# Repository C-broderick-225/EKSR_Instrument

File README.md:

# EKSR_Instrument (Fork)

**This repository is a fork of the original [EKSR_Instrument](https://github.com/magicmicros/EKSR_Instrument) project.**

## Overview
This project serves as the foundation for a new product based on the EKSR_Instrument hardware and firmware. It utilizes an ESP32-S3 microcontroller to receive and decode messages from FarDriver motor controllers over BLE, and displays the processed data on a 2.4" TFT touchscreen display.

## ESP32-S3 BLE Multi-Role Support
The ESP32-S3 (including the ESP32-S3-WROOM-1 module) is capable of acting as both a BLE client (central) and a BLE server (peripheral) simultaneously. This allows the device to connect to a BLE peripheral (such as a Far Driver controller) while also advertising its own BLE service for other clients (such as an Android phone) to connect and receive forwarded data. This multi-role (dual-role) capability is officially supported by Espressif and is useful for BLE proxy/bridge applications.

**Key facts:**
- The ESP32-S3 can operate as both a BLE client and server at the same time (multi-role topology).
- This is supported by the ESP-IDF and ESP-NimBLE host stack.
- Example use case: ESP32-S3 connects to a Far Driver controller as a client, and simultaneously acts as a server to forward data to a mobile app.

**Official documentation:**
- [ESP-IDF BLE Introduction: Bluetooth LE Network Topology](https://docs.espressif.com/projects/esp-idf/en/stable/esp32s3/api-guides/ble/get-started/ble-introduction.html#bluetooth-le-network-topology)
- [ESP-NimBLE API Reference](https://docs.espressif.com/projects/esp-idf/en/stable/esp32s3/api-reference/bluetooth/esp-nimble/index.html)

## Purpose
The goal of this fork is to extend and adapt the original EKSR_Instrument platform for new applications and features. All original design and implementation credit belongs to the original author. This repository will introduce new features, modifications, and documentation specific to the goals of the new product.

## FarDriver BLE Emulator
A FarDriver BLE emulator is included in the `emulator/` directory. This tool allows you to use an ESP32 (such as ESP-WROVER-E) as a BLE peripheral that mimics the FarDriver controller. It is useful for testing the EKSR Instrument firmware without requiring the actual controller hardware.

- The emulator advertises the same BLE service and characteristic UUIDs as the real controller.
- It sends realistic, cyclic data packets for rpm, voltage, temperature, throttle, and more.
- The EKSR Instrument client can connect and display the emulated data as if it were connected to a real FarDriver controller.

For build instructions, customization, and protocol details, see [`emulator/README.md`](emulator/README.md).

## License
See the LICENSE file for details.

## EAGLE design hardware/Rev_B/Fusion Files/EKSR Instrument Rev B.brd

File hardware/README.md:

# Hardware for the EKSR Instrument.

The circuit is pretty straightforward.

The 12V input is dropped to 3.3V by an Alpha & Omega AOZ1284PI buck converter.

The ESP32-S3 controls the ILI9341 based TFT display though SPI and get touch data from the resistive touchcreen, using 4 ADC inputs.

The backlight is controlled with PWM through a N-channel FET.

Rev B adds a input voltage monitor though a 16:1 resistor divider, giving 900mV at 14.4V in.

Programming and log data output is, as usual for the ESP32's, through a 3.3V TTL level serial port.

Communication with the controller is though the built-in BLE in the ESP32-S3 (using Nimble BLE stack).

The board fits into a SZOMK AK-H-15 enclosure.\
This is not the enclosure used for the prototype, but it's the same inner dimensions and have an improved water seal.\
Still, the display have to be sealed against the enclosure, perhaps using a cutout "gasket" from 0.5mm rubber or silicone.

The `.brd` and `.sch` files in the `Fusion Files` folder, is EAGLE V9.x format.\
Project is originally made with Fusion 360/Fusion Electronics.

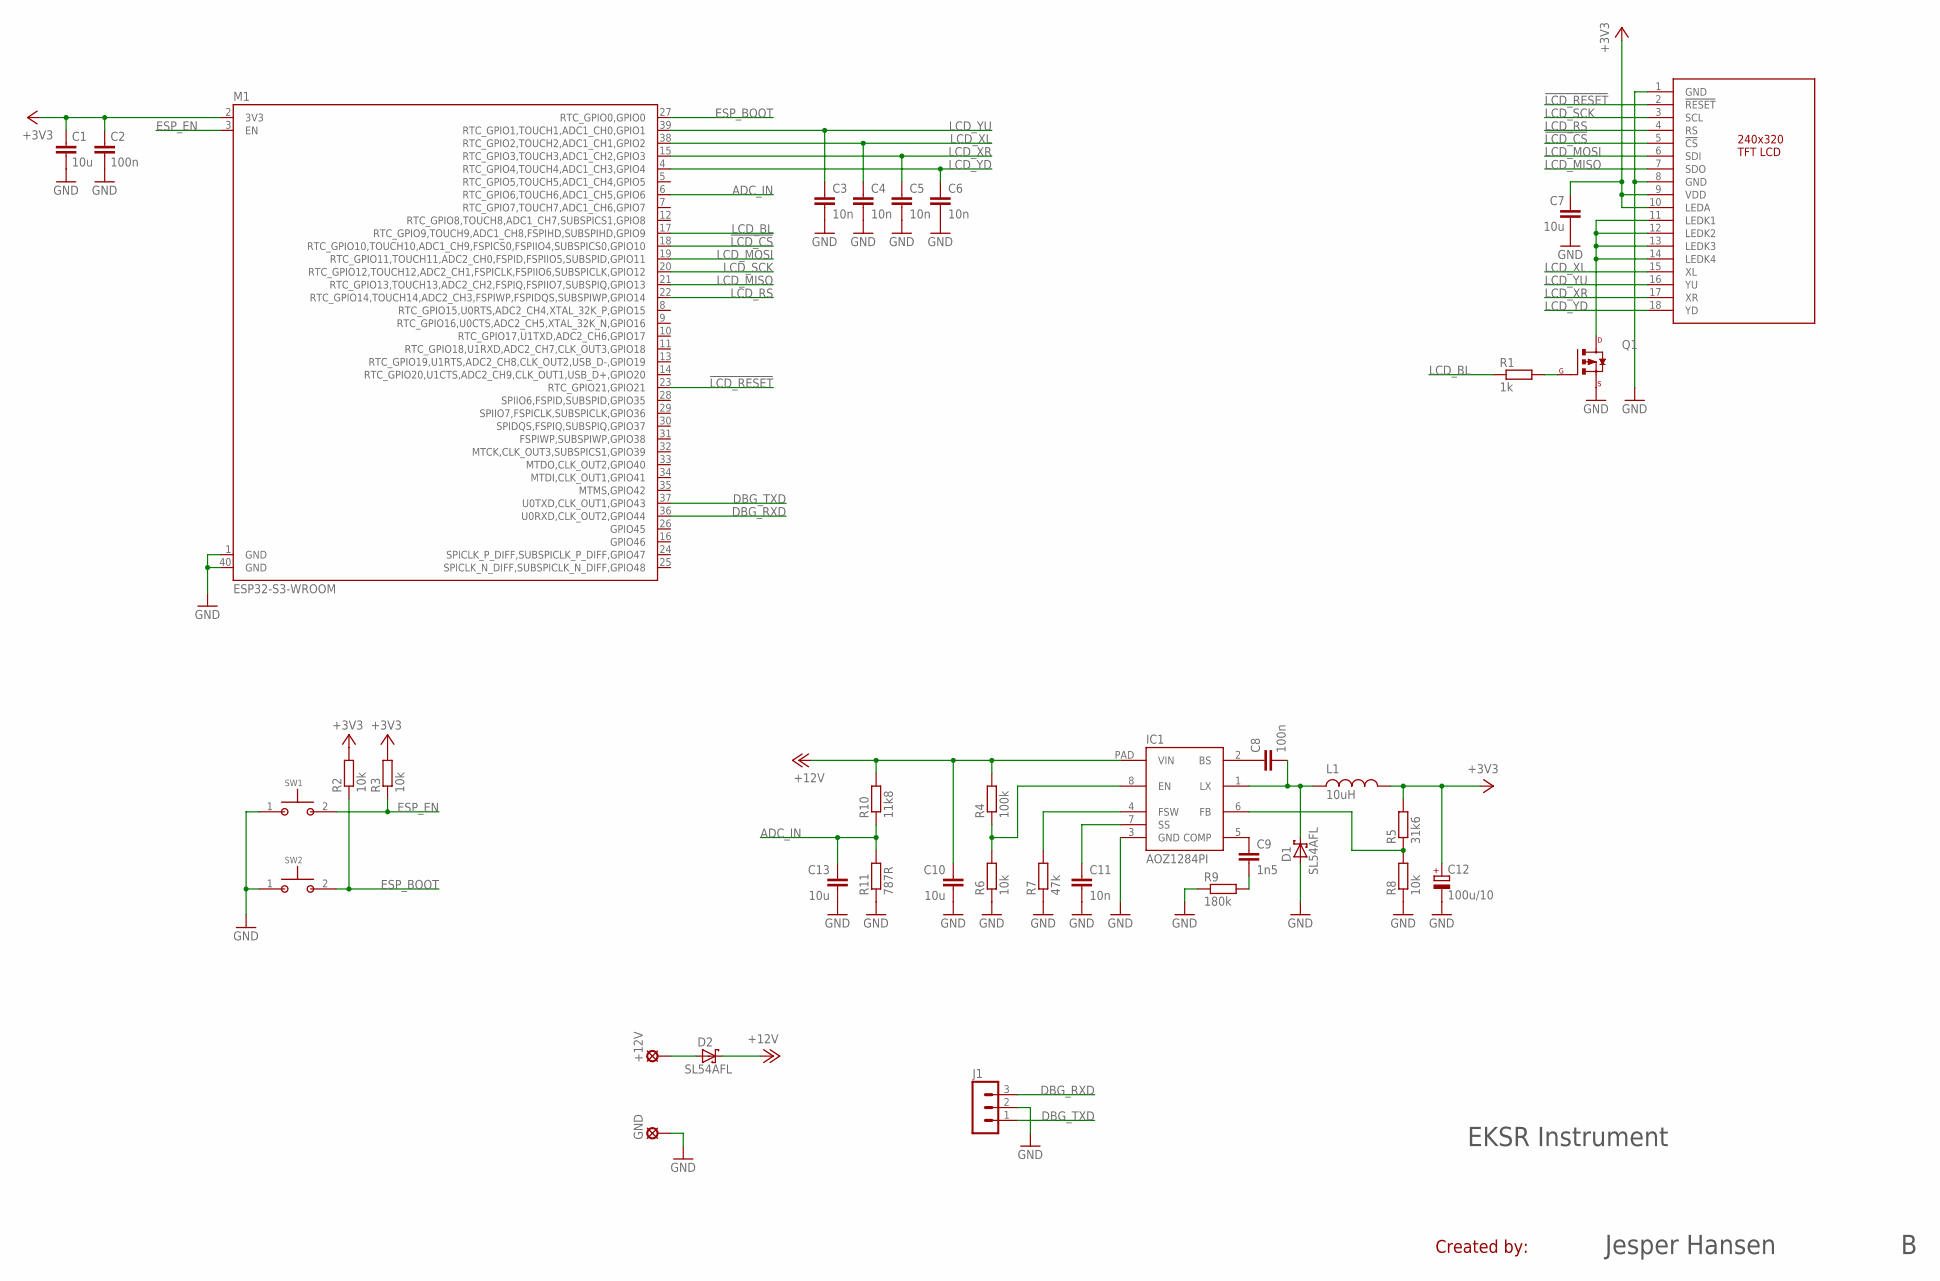
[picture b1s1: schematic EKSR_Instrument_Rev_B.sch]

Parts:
+12V: LSP13
C1, C7, C10, C13: 10u; C0603
C2, C8: 100n; C0603
C3, C4, C5, C6, C11: 10n; C0603
C9: 1n5; C0603
C12: 100u/10; CT3528
D1, D2: SL54AFL; DO221-AC
DISP1: TFT_2.4_A"; TFT_2.4_A2
GND: LSP13
IC1: AOZ1284PI; SO8_EDP
J1: MA03-1W
L1: 10uH; SPM6530
M1: ESP32-S3-WROOM
Q1: MOSFET_P; SOT-23
R1: 1k; R0603
R2, R3, R6, R8: 10k; R0603
R4: 100k; R0603
R5: 31k6; R0603
R7: 47k; R0603
R9: 180k; R0603
R10: 11k8; R0603
R11: 787R; R0603
SW1, SW2: PTS820

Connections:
!LCD_CS: DISP1.5 (!CS), M1.18 (RTC_GPIO10,TOUCH10,ADC1_CH9,FSPICS0,FSP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)
!LCD_RESET: DISP1.2 (!RESET), M1.23 (RTC_GPIO21,GPIO21)
+3V3: C1.1, C2.1, C7.1, C12.+, DISP1.9 (VDD), DISP1.10 (LEDA), L1.2, M1.2 (3V3), R2.2, R3.2, R5.2
+12V: C10.1, D2.C, IC1.PAD (VIN), R4.2, R10.2
ADC_IN: C13.1, M1.6 (RTC_GPIO6,TOUCH6,ADC1_CH5,GPIO6), R10.1, R11.2
DBG_RXD: J1.3, M1.36 (U0RXD,CLK_OUT2,GPIO44)
DBG_TXD: J1.1, M1.37 (U0TXD,CLK_OUT1,GPIO43)
ESP_BOOT: M1.27 (RTC_GPIO0,GPIO0), R2.1, SW2.2
ESP_EN: M1.3 (EN), R3.1, SW1.2
GND: C1.2, C2.2, C3.2, C4.2, C5.2, C6.2, C7.2, C10.2, C11.2, C12.-, C13.2, D1.A, DISP1.1 (GND), DISP1.8 (GND), GND.MP, IC1.3 (GND), J1.2, M1.1 (GND), M1.40 (GND), Q1.2 (P_S), R6.1, R7.1, R8.1, R9.1, R11.1, SW1.1, SW2.1
LCD_BL: M1.17 (RTC_GPIO9,TOUCH9,ADC1_CH8,FSPIHD,SUBSPI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), R1.1
LCD_MISO: DISP1.7 (SDO), M1.21 (RTC_GPIO13,TOUCH13,ADC2_CH2,FSPIQ,FSPII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)
LCD_MOSI: DISP1.6 (SDI), M1.19 (RTC_GPIO11,TOUCH11,ADC2_CH0,FSPID,FSPII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)
LCD_RS: DISP1.4 (RS), M1.22 (RTC_GPIO14,TOUCH14,ADC2_CH3,FSPIWP,FSPI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)
LCD_SCK: DISP1.3 (SCL), M1.20 (RTC_GPIO12,TOUCH12,ADC2_CH1,FSPICLK,FSP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)
LCD_XL: C4.1, DISP1.15 (XL), M1.38 (RTC_GPIO2,TOUCH2,ADC1_CH1,GPIO2)
LCD_XR: C5.1, DISP1.17 (XR), M1.15 (RTC_GPIO3,TOUCH3,ADC1_CH2,GPIO3)
LCD_YD: C6.1, DISP1.18 (YD), M1.4 (RTC_GPIO4,TOUCH4,ADC1_CH3,GPIO4)
LCD_YU: C3.1, DISP1.16 (YU), M1.39 (RTC_GPIO1,TOUCH1,ADC1_CH0,GPIO1)
unnamed: IC1.6 (FB), R5.1, R8.2
unnamed: Q1.1 (P_G), R1.2
unnamed: DISP1.11 (LEDK1), DISP1.12 (LEDK2), DISP1.13 (LEDK3), DISP1.14 (LEDK4), Q1.3 (P_D)
unnamed: +12V.MP, D2.A
unnamed: IC1.8 (EN), R4.1, R6.2
unnamed: C8.1, IC1.2 (BS)
unnamed: IC1.4 (FSW), R7.2
unnamed: C11.1, IC1.7 (SS)
unnamed: C9.2, R9.2
unnamed: C9.1, IC1.5 (COMP)
SW: C8.2, D1.C, IC1.1 (LX), L1.1

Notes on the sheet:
EKSR Instrument
Created by:
Jesper Hansen

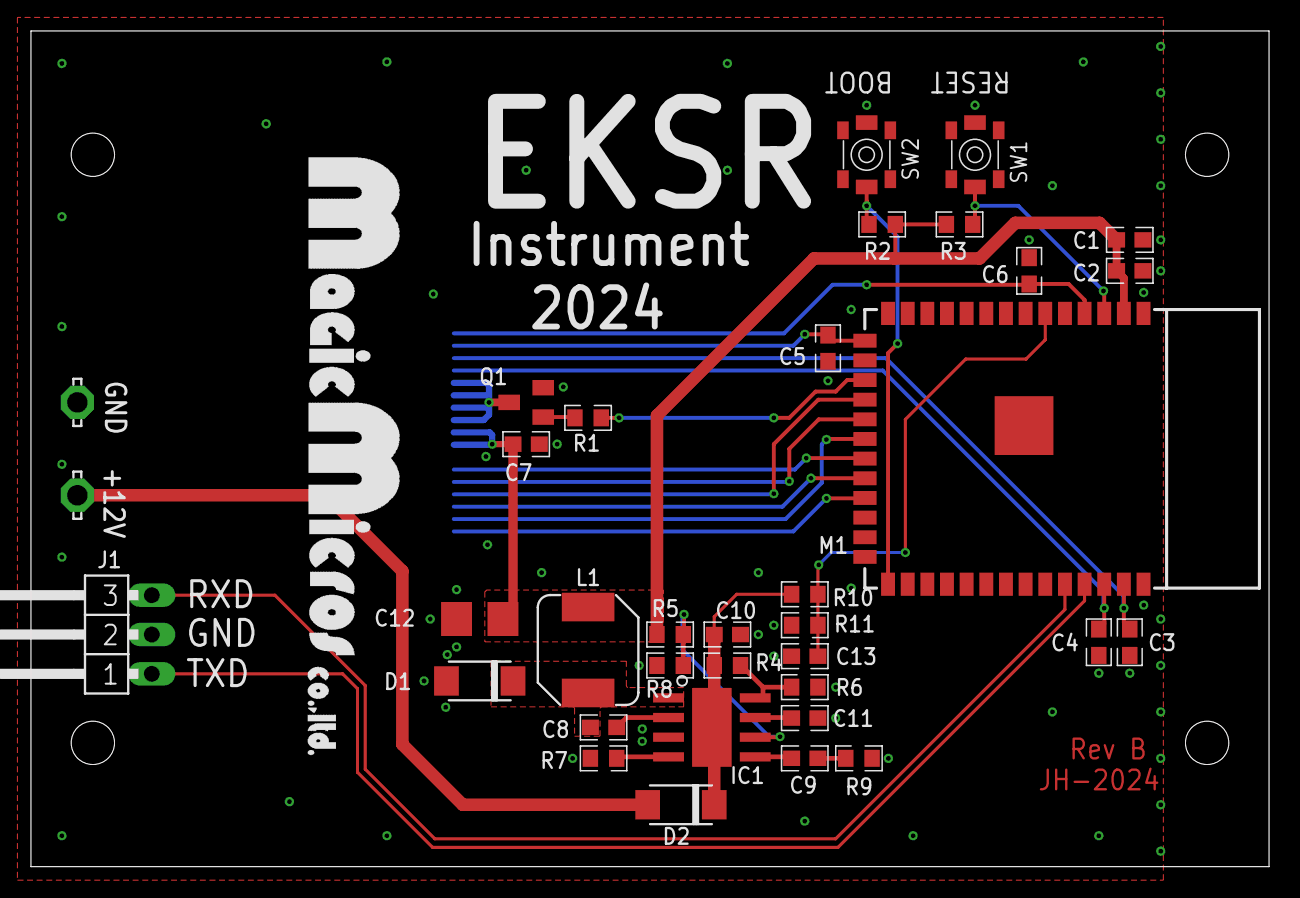
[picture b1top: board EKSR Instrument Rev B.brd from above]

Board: 2 copper layers, 80.0 x 54.0 mm, 36 parts (1 on the bottom side), 30 nets.

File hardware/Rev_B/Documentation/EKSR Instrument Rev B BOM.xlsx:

| Bill Of Materials, EKSR Instrument, Rev B |  |  |  |  |  |  |  |  | 45584
 | Qty | Part | Value | Package | Description | Manufacturer | Manufacturer Partno | Distributor | Distributor Partno | Comments | Cost, single qty
 | 4 | C1,C7,C10,C13 | 10u | C0603 | CAPACITOR, European symbol | Murata Electronics | GRM188R61E106KA73J | Digikey | 490-GRM188R61E106KA73JCT-ND |  | 1.08
 | 2 | C2,C8 | 100n | C0603 | Capacitor Ceramic, X7R, 0603 | TDK Corporation | C1608X7R1E104K080AA | Digikey | 445-1316-1-ND |  | 0.2
 | 5 | C3,C4,C5,C6,C11 | 10n | C0603 | Capacitor Ceramic, X7R, 0603 | Kemet | C0603C103K5RACTU | Digikey | 399-1091-1-ND |  | 0.5
 | 1 | C9 | 1n5 | C0603 | Capacitor Ceramic, X7R, 0603 | Samsung Electro | CL10B152KB8WPNC | Digikey | 1276-6666-1-ND |  | 0.1
 | 1 | C12 | 100u/10 | CT3528 | Capacitor Tantalum, 3528 | AVX Corporation | F931A107KBA | Digikey | 478-8195-1-ND |  | 0.86
 | 2 | D1,D2 | SL54AFL | DO221-AC | Shottky Diode, 40V, 5A, SMA_FL | Micro Commercial | SL54AFL-TP | Digikey | SL54AFL-TPMSCT-ND |  | 1
 | 1 | DISP1 | TFT_2.4_A | TFT_2.4_A | 2.4" TFT LCD with Touch, ILI9341 Controller |  |  | HongKong CCD Limited |  | https://vi.aliexpress.com/item/3256806944734005.html | 3.5
 | 1 | IC1 | AOZ1284PI | SO8_EDP | EZBuckTM 4A Simple Adjustable Buck Regulator | Alpha & Omega Semconductor | AOZ1284PI | Digikey | 785-1689-1-ND |  | 1.38
 | 1 | J1 | DEBUG/PROG | MA03-1W | 3x1 pos 0.1" pin header, RA | AdamTech | PH1RB-03-UA | Digikey | 2057-PH1RB-03-UA-ND |  | 0.12
 | 1 | L1 | 10uH | SPM6530 | Inductor, 10uH, 4.2A, 86mR | TDK Corporation | SPM6530T-100M-HZ | Digikey | 445-180110-1-ND |  | 3.9
 | 1 | M1 | ESP32-S3-WROOM | ESP32-S3-WROOM | ESP32-S3 WROOM module. | Espressif | ESP32-S3-WROOM-1-N16R8 | Digikey | 1965-ESP32-S3-WROOM-1-N16R8CT-ND |  | 0.37
 | 1 | Q1 | DMN3023L-7 | SOT-23 | MOSFET N-CH 30V 6.2A SOT23 | Diodes Inc | DMN3023L-7 | Digikey | DMN3023L-7DICT-ND |  | 0.4
 | 1 | R1 | 1k | R0603 | Resistor, 1%, 0603 | Stackpole Electronics | RMCF0603FT1K00 | Digikey | RMCF0603FT1K00CT-ND |  | 0.1
 | 4 | R2,R3,R6,R8 | 10k | R0603 | Resistor, 1%, 0603 | Stackpole Electronics | RMCF0603FT10K0 | Digikey | RMCF0603FT10K0CT-ND |  | 0.1
 | 1 | R4 | 100k | R0603 | Resistor, 1%, 0603 | Stackpole Electronics | RMCF0603FT100K | Digikey | RMCF0603FT100KCT-ND |  | 0.1
 | 1 | R5 | 31k6 | R0603 | Resistor, 1%, 0603 | Stackpole Electronics | RMCF0603FT31K6 | Digikey | RMCF0603FT31K6CT-ND |  | 0.1
 | 1 | R7 | 47k | R0603 | Resistor, 1%, 0603 | Stackpole Electronics | RMCF0603FT47K0 | Digikey | RMCF0603FT47K0CT-ND |  | 0.1
 | 1 | R9 | 180k | R0603 | Resistor, 1%, 0603 | Stackpole Electronics | RMCF0603FT180K | Digikey | RMCF0603FT180KCT-ND |  | 0.1
 | 1 | R10 | 11k8 | R0603 | Resistor, 1%, 0603 | Stackpole Electronics | RMCF0603FT11K8 | Digikey | RMCF0603FT11K8CT-ND |  | 0.1
 | 1 | R11 | 787R | R0603 | Resistor, 1%, 0603 | Stackpole Electronics | RMCF0603FT787R | Digikey | RMCF0603FT787RCT-ND |  | 0.1
 | 2 | SW1,SW2 | BOOT, RESET | PTS820 | Microminiature SMT Top Actuated Pushbutton | C&K | PTS820 J20M SMTR LFS | Digikey | CKN10505CT-ND |  | 1.98
 | 1 |  | AK-H-15 |  | Enclosure | SZOMK | AK-H-15 | SZOMK Enclosure 03 Store | AK-H-15 | https://vi.aliexpress.com/item/2251832638947727.html | 5.26
 |  |  |  |  |  |  |  |  |  | Total (USD) | 21.449999999999996

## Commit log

2024-10-19 README updates
2025-07-24 Update README to reflect the fork status and purpose of the EKSR_Instrument project
2025-07-24 Revise README to clarify project purpose and update original author link
2025-07-24 Add ESP32-S3 BLE multi-role support section to README, detailing capabilities and use cases
2025-07-24 Add FarDriver BLE emulator section to README, detailing its functionality and usage for testing EKSR Instrument firmware
2025-07-24 Remove FarDriverEmulator.cpp and enhance EKSR_Instrument.ino with additional serial output for debugging FarDriver data updates.
2025-07-24 Refactor FarDriverEmulator.ino to enhance BLE functionality with improved packet generation, connection handling, and debugging output. Introduce custom FarDriver service and optimize data transmissi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
2025-07-24 Remove unused dataTransmissionEnabled variable from FarDriverEmulator.ino to streamline code and improve clarity.
2025-07-24 Refactor LED handling in FarDriverEmulator.ino to centralize control logic, ensuring LED state is managed in the loop() function rather than in connection callbacks.
2025-07-24 Remove FarDriverEmulator.ino and EKSR_Instrument.ino along with associated files to streamline the project structure. Update README to reflect changes and enhance documentation on the BLE emulator's 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
2025-07-24 Update README to note issue with client connection and LED status in BLE emulator
2025-07-24 update code to use new functions
2025-07-24 run auto formatter on arduino ide
2025-07-25 Enhance BLE emulator with dynamic ebike simulation, introducing realistic acceleration, deceleration, and data relationships. Update README for new features and simulation details. Refactor packet ge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
2025-07-25 Enhance BLE emulator and PC display with improved data handling and user interface. Update README for packet structure and usage details. Introduce terminal logging in PC display for better debugging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
2025-07-25 Refactor BLE advertising logic in FarDriverEmulator.ino to ensure reliable reconnection. Reduced packet update interval for faster data transmission. Added error handling for BLE advertising restart 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
2025-07-25 Add connection controls to EKSRDisplayEnhanced for improved user interaction
    Implemented connection and disconnection buttons in the sidebar, enhancing user control over BLE device connections. Added functionality to update button states based on connection status, ensuring a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
2025-07-25 Remove deprecated files and enhance README documentation for EKSR Instrument project
    Deleted unused files including the BLE scanner, lag optimization summary, and terminal display scripts to streamline the project structure. Updated the README to include new features such as data rec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
2025-07-25 Revamp color scheme and button styles in PC display for enhanced accessibility and modern design
    Updated the color palette to align with a modern 2024 design system, improving contrast and accessibility. Refactored button configurations to utilize new color mappings, ensuring a consistent user i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
2025-07-25 Implement terminal message filtering and add custom checkbox for enhanced user control
    Introduced a filtering system for terminal messages, allowing users to selectively display log messages based on their severity. Added a new ModernCheckbox class for improved checkbox styling and hov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
2025-07-28 Add BLE device management features to EKSRDisplayEnhanced
    Introduced a new section for displaying and managing BLE devices within the EKSRDisplayEnhanced interface. This includes a device list with refresh functionality, improved connection handling for bot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
2025-07-29 Remove deprecated files and enhance project structure for EKSR Instrument PC Display
    Deleted the ENHANCED_README.md, install_enhanced.py, pc_display_enhanced.py, requirements_enhanced.txt, and run_enhanced.py files to streamline the project and eliminate unused components. This clean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
2025-09-04 Enhance EKSR Instrument Emulator Suite with new Hall Motor Emulator and improved FarDriver BLE Emulator
    Added a new Hall Motor Emulator for simulating BLDC motor Hall sensor signals, enabling bench testing of motor controllers without physical motors. Updated the FarDriver BLE Emulator to include CRC-1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
2025-09-04 Refactor EKSRDisplayEnhanced to improve BLE device management and connection handling
    Updated the EKSRDisplayEnhanced interface to enhance BLE device management features, including a more responsive device list and improved connection handling for FarDriver and YuanQu devices. This up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
2025-09-04 Remove ESP32 Fardriver BLE Controller code and associated README documentation
    Deleted the ESP32_Fardriver_BLE_Controller.ino file and its README.md to streamline the project by removing unused components. This cleanup enhances maintainability and focuses the codebase on active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
